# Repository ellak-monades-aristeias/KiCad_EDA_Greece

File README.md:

# Περιγραφή έργου KiCad_EDA_Greece
Αυτό το repository [https://github.com/ellak-monades-aristeias/KiCad_EDA_Greece](https://github.com/ellak-monades-aristeias/KiCad_EDA_Greece) δεν είναι ένα τυπικό λογισμικό, αλλά ένα έργο που έχει ως σκοπό την προώθηση του λογισμικού [Kicad](http://kicad.org/) στους Έλληνες χρήστες. Αυτό γίνεται υλοποιώντας τρεις ενέργειες.

* Πλήρης εξελληνισμός του περιβάλλοντος του KiCad [https://github.com/ellak-monades-aristeias/KiCad_EDA_Greece/tree/master/work/translation]
* Ανάπτυξη μίας απλής ηλεκτρονικής συσκευής ανοιχτού υλικού με το KiCad ([περισσότερες πληροφορίες](work/pcb/usb2uart/README.md)) [https://github.com/ellak-monades-aristeias/KiCad_EDA_Greece/tree/master/work/pcb/usb2uart]
* Συγγραφή ενός οδηγού εκμάθησης (tutorial) χρήσης του KiCad στα Ελληνικά χρησιμοποιώντας την ηλεκτρονική συσκευή ανοιχτού υλικού ως βάση [https://github.com/ellak-monades-aristeias/KiCad_EDA_Greece/tree/master/work/tutorial/tutorial_published]

Τα αρχεία και για τις τρεις ενέργειες αποτελούν τα αρχεία αυτού του repository. Μπορείτε να βρείτε περισσότερες πληροφορίες και για τις τρεις ενέργειες στο [KiCad_EDA_Greece Wiki](https://github.com/ellak-monades-aristeias/KiCad_EDA_Greece/wiki).

#English description of project KiCad_EDA_Greece
This repository [https://github.com/ellak-monades-aristeias/KiCad_EDA_Greece](https://github.com/ellak-monades-aristeias/KiCad_EDA_Greece) is not a typical software package, but it is a project with the intent to promote the software application named [Kicad](http://kicad.org/) to Greek users. This is implemented through three means.

* Full localization of KiCad's user interface [https://github.com/ellak-monades-aristeias/KiCad_EDA_Greece/tree/master/work/translation]
* Development of a simple, open hardware electronic device using KiCad ([more information](work/pcb/usb2uart/README.md)) [https://github.com/ellak-monades-aristeias/KiCad_EDA_Greece/tree/master/work/pcb/usb2uart]
* Write a detailed KiCad tutorial in Greek, using the above electronic device as a practical example [https://github.com/ellak-monades-aristeias/KiCad_EDA_Greece/tree/master/work/tutorial/tutorial_published]

The files for all three above actions are the files of this repository. 
You can find more information on all three actions in the [KiCad_EDA_Greece Wiki](https://github.com/ellak-monades-aristeias/KiCad_EDA_Greece/wiki).

# Λόγος ύπαρξης
Το λογισμικό KiCad είναι ένα ιδιαίτερα ισχυρό πρόγραμμα ηλεκτρονικής σχεδίασης (EDA) το οποίο υποστηρίζεται από μια μεγάλη και ενεργή ομάδα προγραμματιστών, καθώς και από το [CERN](http://home.web.cern.ch/).  
Παρότι το KiCad είναι ένα εξαιρετικά χρήσιμο και δυνατό εργαλείο σχεδίασης, δεν έχει τύχει της αναγνώρισης που του αξίζει στην Ελλάδα, καθώς οι χρήστες με περιορισμένους οικονομικούς πόρους συχνά επιλέγουν δωρεάν, αλλά κλειστές λύσεις.
Πιστεύουμε ότι ο λόγος που δεν προτιμάται το KiCad είναι η απουσία πλήρους μετάφρασης της διεπαφής του προγράμματος και η απότομη καμπύλης εκμάθησης του. 
Αυτά τα δύο στοιχεία στοχεύει να ανατρέψει αυτό το έργο.

# Εγκατάσταση και χρήση του έργου
Για οδηγίες εγκατάστασης και χρήσης του έργου δείτε το αρχείο [README_users.md](README_users.md).

# Συνεισφορά στο έργο
Για οδηγίες συνεισφοράς στο έργο δείτε το αρχείο [README_developers.md](README_developers.md).

# Χρήστες του έργου
Το εξελληνισμένο λογισμικό ηλεκτρονικής σχεδίασης KiCad μαζί με το ελληνικό tutorial μπορεί να φανεί χρήσιμο σε άτομα, οργανισμούς και επιχειρήσεις οι οποίοι θέλουν να μπορούν να σχεδιάσουν ηλεκτρονικά κυκλώματα και πλακέτες για προσωπικούς, επαγγελματικούς, και εκπαιδευτικούς λόγους. 
Σαν παράδειγμα χρηστών σε κάθε κατηγορία μπορούν να σημειωθούν οι χομπίστες ηλεκτρονικών, οι νεοφυείς επιχειρήσεις με περιορισμένους πόρους, και τα σχολεία ή ΤΕΙ.

# Οθόνη Ελληνικού περιβάλλοντος KiCad

# Ελάχιστες απαιτήσεις (προαπαιτούμενα)
Οι ελάχιστες απαιτήσεις για χρήση του εξελληνισμένου περιβάλλοντος KiCad είναι το λογισμικό KiCad. Το KiCad (έκδοση 4.0) τρέχει σε οποιονδήποτε υπολογιστή που τρέχει ένα από τα υποστηριζόμενα λειτουργικά συστήματα.
Για τον οδηγό εκμάθησης (tutorial) χρήσης του KiCad η μόνη απαίτηση είναι ένα πρόγραμμα προβολής αρχείων pdf. Για τη συσκευή ανοιχτού λογισμικού απαιτείται επίσης το λογισμικό KiCad.

# Τελικά Αποτελέσματα Έργου (Παραδοτέα)

* Παραδοτέο 1: [οδηγός εκμάθησης/tutorial χρήσης του KiCad στα Ελληνικά](https://github.com/ellak-monades-aristeias/KiCad_EDA_Greece/blob/master/work/tutorial/tutorial_published/tutorial_kicad_issue01_00.pdf)

* Παραδοτέο 2: [αρχεία κυκλώματος ανοιχτού υλικού](https://github.com/ellak-monades-aristeias/KiCad_EDA_Greece/tree/master/work/pcb/usb2uart)

* Παραδοτέο 3: [αρχεία μετάφρασης KiCad](https://github.com/ellak-monades-aristeias/KiCad_EDA_Greece/blob/master/work/translation/kicad.po)

# Άδεια χρήσης και πνευματικά δικαιώματα

Το περιεχόμενο αυτού του έργου κυκλοφορεί κάτω από άδειες EUPL v1.1 και CC-BY-SA 4.0.

**Για να δείτε το περιεχόμενο αυτών των αδειών επισκεφθείτε τα  http://creativecommons.org/licenses/by-sa/4.0/deed.el και http://ec.europa.eu/idabc/eupl.html**

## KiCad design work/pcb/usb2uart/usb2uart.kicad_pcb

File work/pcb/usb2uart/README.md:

## USB2UART: μετατροπέας USB σε 3,3V UART ανοιχτού υλικού

---

Σχηματικό κύκλωμα και σχεδίαση πλακέτας για έναν μετατροπέα USB σε 3,3V UART ανοιχτού υλικού. Υλικό για ελληνικό οδηγό εκμάθησης του KiCad.

### Το USB2UART είναι ένας βασικός μετατροπέας USB σε 3,3V UART με τα παρακάτω χαρακτηριστικά:

Η συσκευή ονομάζεται USB2UART και είναι ένας μετατροπέας USB σε 3,3V UART, βασισμένος στο ολοκληρωμένο CP2104 από την εταιρεία Silicon Labs. Συνδέεται με έναν σύνδεσμο USB type B από τη μία πλευρά και έναν απλό σύνδεσμο τεσσάρων ακροδεκτών από την άλλη. Περιλαμβάνει LED ένδειξης on/off και LED ένδειξης αποστολής/παραλαβής RX/TX.

* Βασισμένος στο ολοκληρωμένο CP2104 από την εταιρεία Silicon Labs.
* Υποστηρίζεται από τα περισσότερα σύγχρονα λειτουργικά συστήματα ως εικονική σειριακή θύρα.
* Διαθέτει έναν σύνδεσμο USB τύπου B από τη μία πλευρά και έναν απλό σύνδεσμο τεσσάρων ακροδεκτών (pin header) από την άλλη
* Περιλαμβάνει LED ένδειξης on/off και LED ένδειξης αποστολής/παραλαβής RX/TX.
* Έχει υλοποιηθεί ως πλακέτα τυπωμένου κυκλώματος (PCB) δύο επιπέδων χρησιμοποιώντας το [KiCAD EDA software suite](http://www.kicad.org).
* Ανοιχτό υλικό.

---

### Διάγραμμα μπλοκ

---

### Λίστα αρχείων

* **README.md:** αυτό το αρχείο
* **usb2uart.pro:** αρχείο έργου KiCAD
* **usb2uart.sch:** σχηματικό κύκλωμα
* **usb2uart.pdf:** σχηματικό κύκλωμα τυπωμένο σε PDF
* **usb2uart.lib:** βιβλιοθήκη προσαρμοσμένων εξαρτημάτων
* **usb2uart-cache.lib:** προσωρινή αποθήκευση βιβλιοθήκης όλων των εξαρτημάτων
* **usb2uart.dcm:** βιβλιοθήκη τεκμηρίωσης εξαρτημάτων
* **usb2uart.net:** λίστα δικτύων
* **usb2uart.kicad_pcb:** σχεδίαση πλακέτας
* **usb2uart.csv:** λίστα υλικών (BOM)
* **usb2uart.pretty/:** βιβλιοθήκη προσαρμοσμένων αποτυπωμάτων
* **contrib/:** 3Δ μοντέλα από τρίτους. Πολλές ευχαριστίες στον [Walter](http://smisioto.no-ip.org/elettronica/kicad/kicad-en.htm) για τη διανομή της δουλειάς του σε [CC-BY-SA 3.0](http://creativecommons.org/licenses/by-sa/3.0/)
* **datasheets/:** εγχειρίδια/φύλλα δεδομένων (datasheets) για όλα τα εξαρτήματα
* **images/:** διάφορες εικόνες
* **mfg/usb2uart.drl:** αρχείο διάτρησης excellon CNC
* **mfg/usb2uart-all.pos:** αρχείο τοποθέτησης εξαρτημάτων SMD για μηχανές ανύψωσης και τοποθέτησης
* **mfg/gerber/:** αρχεία gerber

---

### Άδεια χρήσης και πνευματικά δικαιώματα

**© 2014-2015 Logikon Labs.**

**Όλα τα αρχεία σχεδίασης και παραγωγής είναι διαθέσιμα με άδειες [Creative Commons Attribution-ShareAlike 4.0 International License](http://creativecommons.org/licenses/by-sa/4.0/).**

**Για να δείτε το περιεχόμενο αυτής της άδειας χρήσης επισκεφθείτε το http://creativecommons.org/licenses/by-sa/4.0/deed.el.**

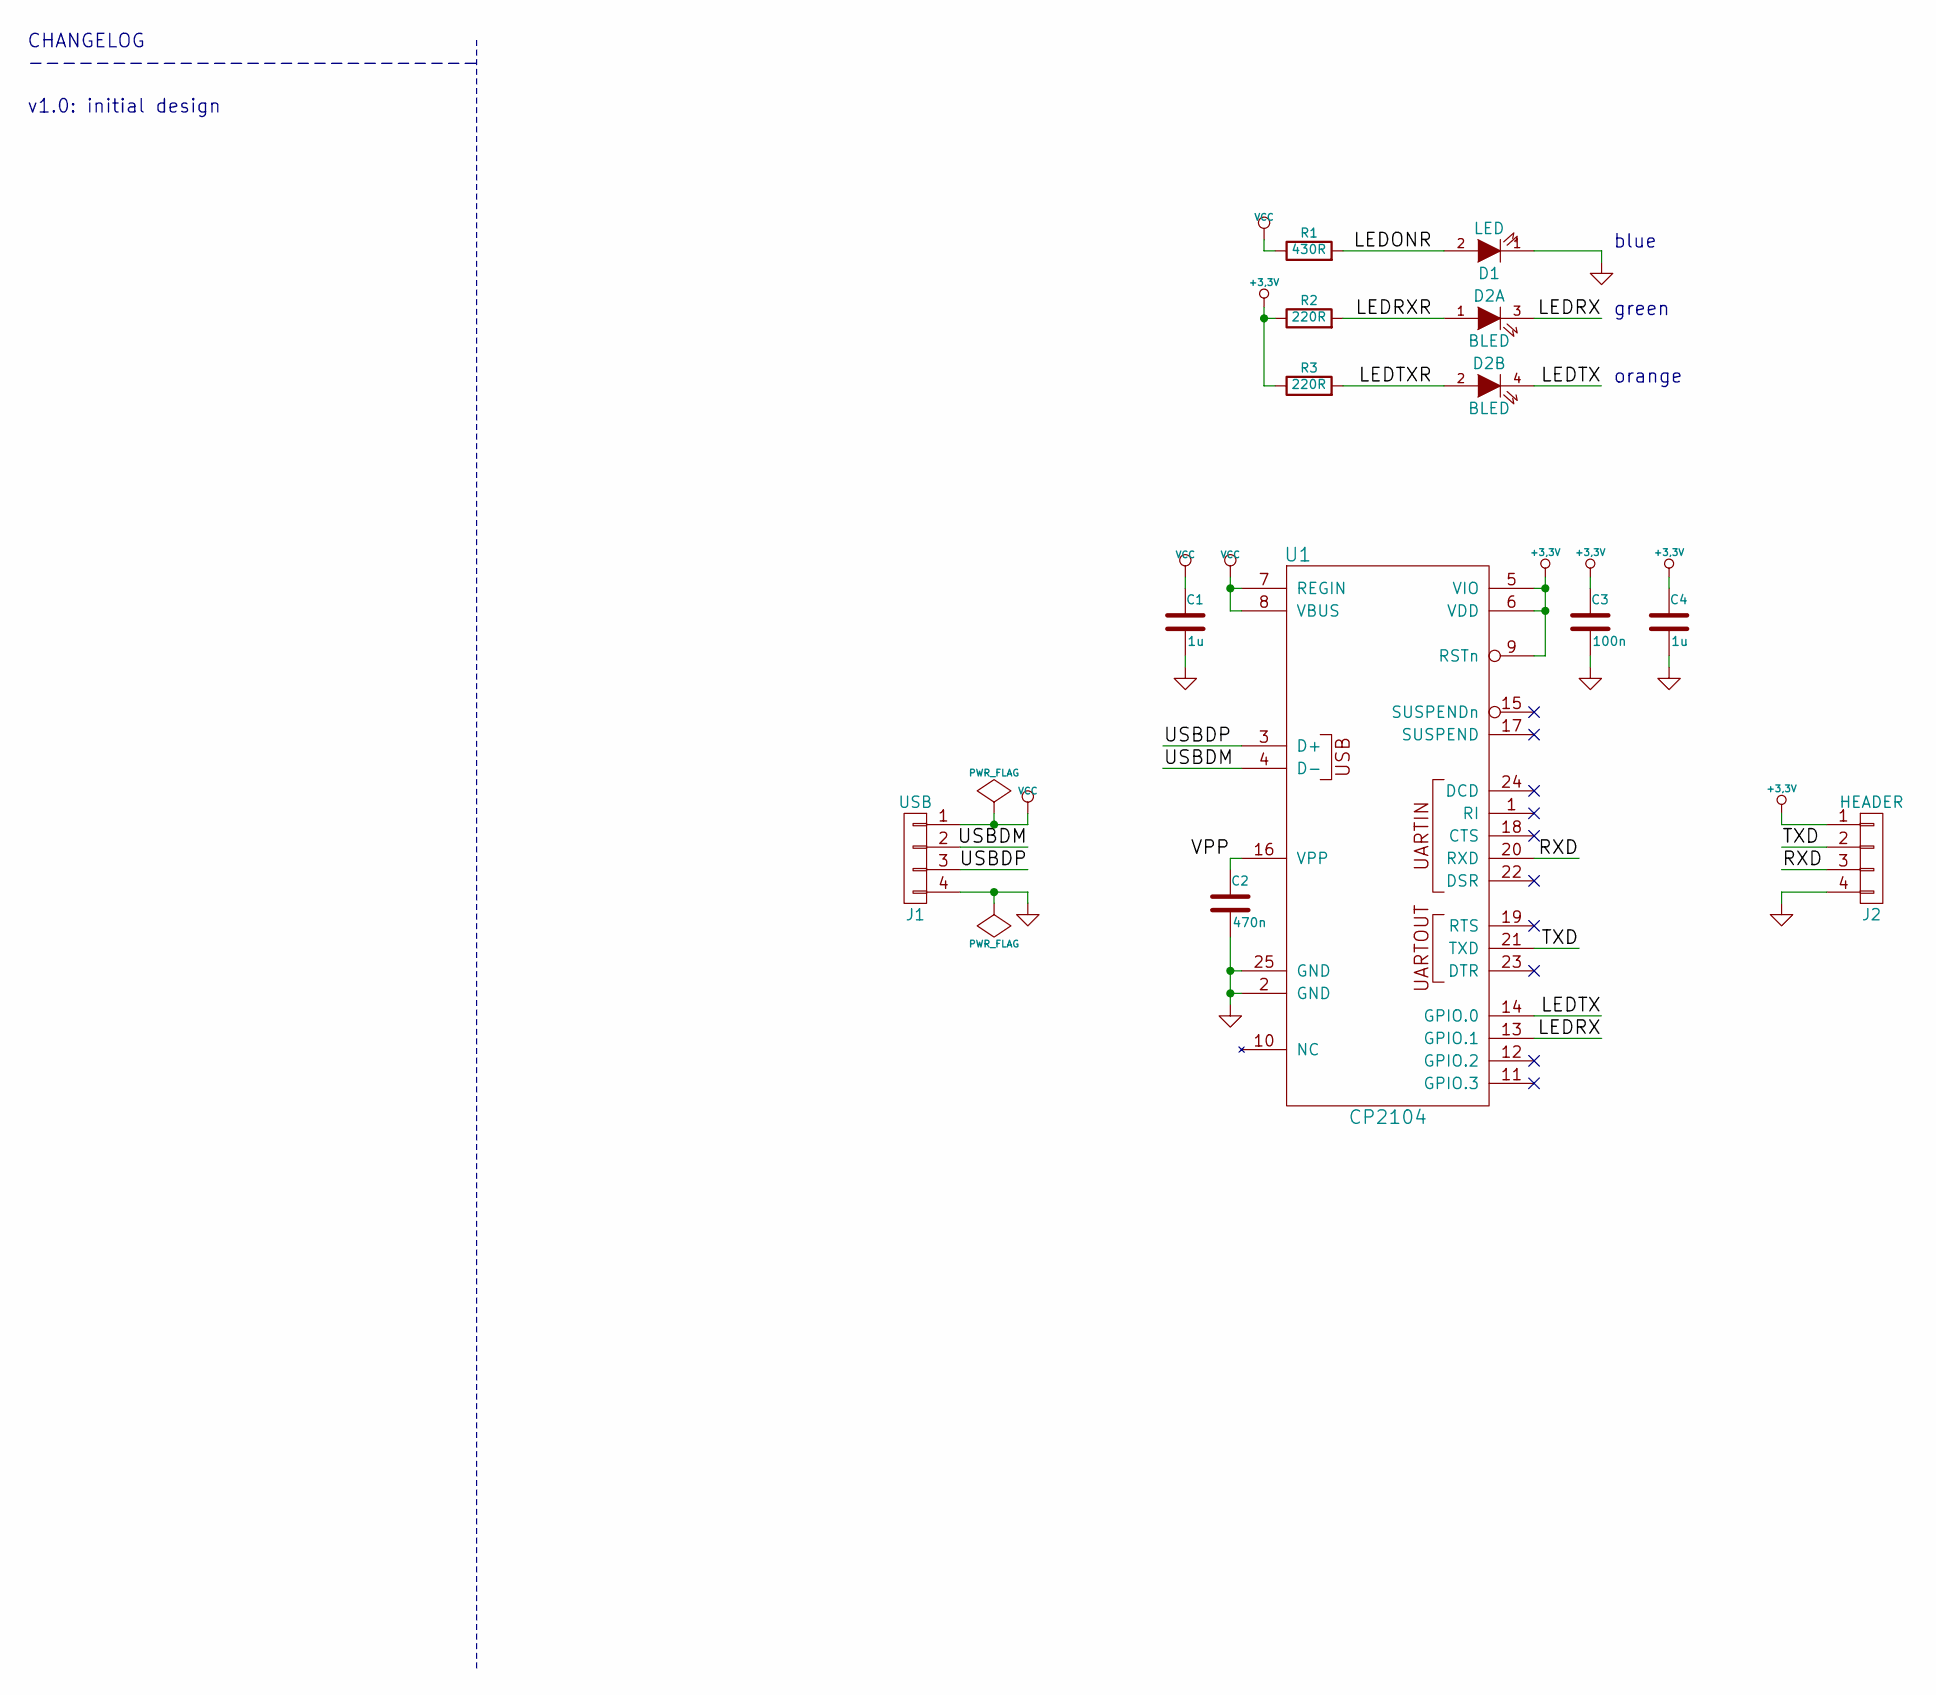
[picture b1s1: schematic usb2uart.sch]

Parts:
C1, C4: 1u; C_0402
C2: 470n; C_0402
C3: 100n; C_0402
D1: LED; LED-0603
D2: BLED; bled_0603
J1: USB; USB_B
J2: HEADER; Pin_Header_Angled_1x04
R1: 430R; R_0402
R2, R3: 220R; R_0402
U1: CP2104; qfn24

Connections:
+3.3V: C3.1, C4.1, J2.1, R2.1, R3.1, U1.5 (VIO), U1.6 (VDD), U1.9 (RSTn)
/LEDONR: D1.2 (A), R1.2
/LEDRX: D2.3 (K), U1.13 (GPIO.1)
/LEDRXR: D2.1 (A), R2.2
/LEDTX: D2.4 (K), U1.14 (GPIO.0)
/LEDTXR: D2.2 (A), R3.2
/RXD: J2.3, U1.20 (RXD)
/TXD: J2.2, U1.21 (TXD)
/USBDM: J1.2, U1.4 (D-)
/USBDP: J1.3, U1.3 (D+)
/VPP: C2.1, U1.16 (VPP)
GND: C1.2, C2.2, C3.2, C4.2, D1.1 (K), J1.4, J2.4, U1.2 (GND), U1.25 (GND)
VCC: C1.1, J1.1, R1.1, U1.7 (REGIN), U1.8 (VBUS)

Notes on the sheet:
CHANGELOG --------------------------- v1.0: initial design
blue
green
orange

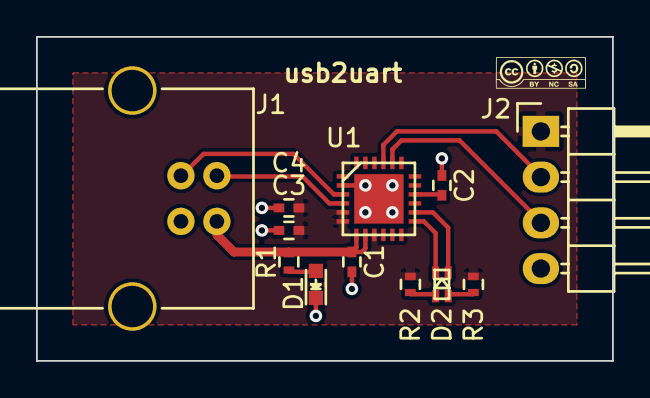
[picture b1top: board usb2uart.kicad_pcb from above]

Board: 2 copper layers, 32.0 x 18.0 mm, 12 parts (0 on the bottom side), 13 nets.

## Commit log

2015-08-26 [doc] Συγγραφή readme.md
2015-08-27 [transl] Προσθήκη ελληνικού .po από bazaar commit revno: 866
2015-08-27 [transl] Ανανεώθηκαν τα αρχεία .po με βάση τον κώδικα με github hash 2e4136720dbe98facf8888f714fa4418228af49b
2015-08-27 [transl] Ολοκλήρωση μετάφρασης αρχικής οθόνης (εκτός προγραμμάτων)
2015-08-28 [transl] Ολοκλήρωση μετάφρασης αρχικής οθόνης και υποεπιλογών (εκτός προγραμμάτων)
2015-09-01 [transl] Μετάφραση κύριων εννοιών (via, schematic, κοκ)
2015-09-01 [transl] Μετάφραση βασικών εννοιών και μερικώς EEschema
2015-09-02 [transl] Μετάφραση μεγαλύτερου μέρους μενού EEschema
2015-09-03 [transl] Ολοκλήρωση μενού και κουμπιών αρχικής σελίδας Eeschema
2015-09-03 [transl] Ολοκλήρωση μενού έως και Τοποθέτηση (και παιδιών) αρχικής σελίδας Eeschema
2015-09-04 [transl] Ολοκλήρωση μενού έως και Προτιμήσεις (και παιδιών) αρχικής σελίδας Eeschema
2015-09-04 [transl] Ολοκλήρωση αρχικής σελίδας component editor
2015-09-04 [transl] Μετάφραση strings σχετικά με αρχεία
2015-09-10 [transl] Μετάφραση μενού (πλήρες βάθος) σε component editor
2015-09-10 [transl] Ολοκλήρωση μετάφρασης component editor
2015-09-10 [transl] Μετάφραση Eeschema
2015-09-11 [pcb] Πρώτη έκδοση (ημιτελής) του κυκλώματος
2015-09-11 [transl] Ολοκλήρωση μετάφρασης Eeschema, component editor (99%)
2015-09-14 [transl] Μετάφραση κειμένων CvPCB
2015-09-14 [transl] Ολοκλήρωση μετάφρασης Cvpcb και σχετικών εργαλείων (99%)
2015-09-14 [transl] Αλλαγή μετάφραση annotate και reference
2015-09-14 [transl] Μετάφραση κειμένων PCBnew
2015-09-15 [transl] Μετάφραση αρχικής οθόνης footprint editor
2015-09-15 [transl] Ολοκλήρωση μετάφρασης footprint editor (99%)
2015-09-16 [transl] Μετάφραση γενικών κειμένων
2015-09-17 [transl] Ολοκλήρωση μετάφρασης αρχικής σελίδας PCBnew
2015-09-17 [transl] Ολοκλήρωση όλων των fuzzy
2015-09-18 [transl] Ολοκλήρωση μετάφρασης PCBnew (έως και δεύτερο επίπεδο)
2015-09-18 [transl] Μετάφραση διάφορων κειμένων
2015-09-22 [transl] Ολοκλήρωση μετάφρασης 100% (προ ελέγχων)
2015-09-23 [transl] Διορθώσεις μεταφράσεων, ορισμός συντομεύσεων &
2015-09-23 [transl] Ορισμός συντομεύσεων &
2015-09-23 [transl] Αλλαγή γλώσσας σε el
2015-09-23 [transl] Διαγραφή περιττών σχολίων
2015-09-24 [transl] Ορισμός σωστών συντομεύσεων (&) σε όλα τα μενού
2015-09-25 [transl] Διορθώσεις κειμένων
2015-09-25 [pcb] πρώτη ολοκληρωμένη έκδοση κυκλώματος, μαζί με αρχεία παραγωγής
2015-09-25 [pcb] fixed typo in README.md
2015-09-25 ενημέρωση κεντρικού αρχείου README
2015-10-02 [tut] Σχεδιασμός κεφαλαίων και περιεχομένου του tutorial
2015-10-07 [transl] Ανανέωση Ελληνικού .po με πηγαίο κώδικα από revision 6215
2015-10-07 [transl] 100% πλήρης και ελεγμένη μετάφραση για revision 6215 του πηγαίου κώδικα
2015-10-07 ανανέωση .gitignore
2015-10-07 [tut] Δημιουργία αρχείου tutorial, πρώτα κείμενα
2015-10-07 [tut] Ολοκλήρωση κεφαλαίου δημιουργίας σχηματικού
2015-10-08 [tut] Προσθήκη αρχείου pdf για το tutorial
2015-10-08 Προσθήκη οδηγιών εγκατάστασης
2015-10-08 [tut] Ολοκλήρωση κεφαλαίου προσθήκης εξαρτημάτων
2015-10-08 [tut] Κείμενα κεφαλαίου δημιουργίας εξαρτημάτων
2015-10-09 [tut] Διόρθωση κεφαλαίου προσθήκης εξαρτημάτων
2015-10-12 [tut] Ολοκλήρωση κεφαλαίου προσθήκης/επεξεργασίας εξαρτημάτων πολλών μερών
2015-10-13 Προσθήκη αρχείων για βήματα tutorial
2015-10-13 [tut] Ολοκλήρωση tutorial σχηματικού
2015-10-14 [tut] Ολοκλήρωση κεφαλαίου οριστικής τοποθέτηση αποτυπωμάτων
2015-10-14 Ενημέρωση README.md
2015-10-14 Δημιουργία αρχείου 'ταυτότητα έργου'
2015-10-14 [tut] Ολοκλήρωση tutorial, πρώτη έκδοση
2015-10-14 Προσθήκη αρχείου .gitignore
2015-10-14 [transl] Μικρές διορθώσεις μετάφρασης
2015-10-14 [tut] Προσθήκη εικόνων στο tutorial
2015-10-15 [tut] Αναθεώρηση κεφαλαίου για αρχεία που χρησιμοποιεί το Kicad
2015-10-15 [tut] Ολοκλήρωση tutorial (1.0)
2015-10-20 Ενημέρωση αρχείων .md
2015-10-20 Προσθήκη ταυτότητας έργου σε pdf
2015-10-23 Προσθήκη αρχείων .md για χρήστες και developers
2015-10-23 Ενημέρωση ταυτότητας έργου
2015-10-23 Ενημέρωση οδηγιών για developers
2015-10-30 [transl] Ανανέωση μετάφρασης για αρχεία κώδικα bzr revision 6286
2015-11-04 [transl] Ανανέωση μετάφρασης για αρχεία κώδικα bzr revision 6298
2015-11-04 [transl] Διορώσεις μετάφρασης
2015-11-05 Ανανέωση οδηγιών για developers
2015-11-05 [transl] Διορθώσεις μετάφρασης
2015-11-05 [tut] Ανανέωση tutorial, διόρθωση λαθών, νέα έκδοση (1.1)
2015-11-06 [tut] Ανανέωση tutorial, διόρθωση λαθών, νέα έκδοση (1.2)
2015-11-06 [tut] Ανανέωση tutorial, προσθήκη νέων αρχείων για ενδιάμεσα στάδια, νέα έκδοση (1.5)
2015-11-16 Αγγλική περιγραφή έργου στο README.md
2015-11-20 [transl] Ανανέωση μετάφρασης (rev 6326)
2015-11-20 Ανανέωση README.md με αναφορές στο Wiki
2015-11-23 Διόρθωση τυπογραφικού λάθους στο README.md
2015-11-24 Προσθήκη links προς αρχεία στο README.md
2016-01-03 [transl] Ενημερωση μεταφρασης απο bzr 6413
2016-01-03 [transl] Ολοκλήρωση μεταφρασης bzr 6413
2016-03-25 [transl] Ενημερωση μεταφρασης απο bzr 6648
2016-03-25 [transl] Ολοκλήρωση μετάφρασης απο bzr 6648
2016-04-09 Ενημέρωση αμετάφραστων κειμένων από bzr commit 6677
2016-06-12 [transl] Ολοκλήρωση μετάφρασης απο bzr 6677
2016-06-12 [transl] Ενημέρωση αμετάφραστων αρχείων από bzr 6923
2016-06-12 [transl] Ολοκλήρωση μετάφρασης απο bzr 6923
2016-06-18 [transl] Ενημέρωση αμετάφραστων αρχείων από bzr 6941
2016-06-18 [transl] Ολοκλήρωση μετάφρασης από KiCad source code bzr commit 6941
2016-06-25 [transl] Ενημέρωση αμετάφραστων αρχείων από KiCad source code bzr commit 6946
2016-07-02 [transl] Ενημέρωση αμετάφραστων αρχείων από KiCad source code bzr commit 6960
2016-09-10 [transl] Ενημέρωση αμετάφραστων αρχείων από KiCad source code git commit 7318238daa
2016-12-08 [transl] Ολοκλήρωση μετάφρασης από KiCad source code commit 7318238daa
2016-12-08 [transl] Ενημέρωση αμετάφραστων αρχείων από KiCad source code git commit 3d89fb640a
2016-12-25 [transl] Ολοκλήρωση μετάφρασης από KiCad source code commit 3d89fb640a
2017-01-28 [transl] Ενημέρωση αμετάφραστων αρχείων από KiCad source code commit d0c46a81d9
2017-01-28 [transl] Ολοκλήρωση μετάφρασης από KiCad source code commit d0c46a81d9
2017-02-25 [transl] Ενημέρωση αμετάφραστων αρχείων από KiCad source code commit e6de99cc86
2017-02-25 [transl] Ολοκλήρωση μετάφρασης από KiCad source code commit e6de99cc86
2017-09-27 [transl] Ενημέρωση αμετάφραστων αρχείων από KiCad source code commit 9ca3f632a2
2017-11-18 [transl] Ολοκλήρωση μετάφρασης από KiCad source code commit 9ca3f632a2
2017-11-18 [transl] Ενημέρωση αμετάφραστων αρχείων από KiCad source code commit d5d08d3677
2018-04-06 [transl] Ενημέρωση αμετάφραστων αρχείων από KiCad source code commit 94dbcc7199
2018-09-23 [transl] Ενημέρωση αμετάφραστων αρχείων από KiCad source code commit ae13e441af
2018-10-07 [transl] Work In Progress μετάφραση από KiCad source code commit ae13e441af
2018-10-07 [transl] Ενημέρωση αμετάφραστων αρχείων από KiCad source code commit 1ee579c821
2018-11-27 [transl] Ενημέρωση αμετάφραστων αρχείων από KiCad source code commit db07b43674
2019-01-12 [transl] Work In Progress μετάφραση από KiCad source code commit db07b43674
2019-01-12 [transl] Ενημέρωση αμετάφραστων αρχείων από KiCad source code commit a0a4e5e18d
2019-04-28 [transl] Ενημέρωση αμετάφραστων αρχείων από KiCad source code commit e808c7f956
2019-05-04 [transl] Ενημέρωση αμετάφραστων αρχείων από KiCad source code commit f87754848e
2019-05-05 [transl] Ενημέρωση αμετάφραστων από KiCad 5.1.0, work in progress μετάφραση απομένει 17%
2019-05-05 [transl] Ενημέρωση αμετάφραστων αρχείων από KiCad source code commit f87754848e, μέσω kicad-i18n/update-po-files.sh
2019-07-03 work in progress μετάφραση απομένει 16%
2019-07-03 [transl] Ενημέρωση αμετάφραστων αρχείων από KiCad source code commit c715a22e1c
2019-09-09 [transl] work in progress μετάφραση απομένει 22%
2019-09-09 [transl] Ενημέρωση αμετάφραστων αρχείων από KiCad source code commit 8dd8740fa3
2019-09-09 [transl] work in progress μετάφραση απομένει 25%
2019-09-12 [transl] work in progress μετάφραση απομένει 18%
2019-09-16 [transl] work in progress μετάφραση απομένει 16%
2019-09-17 [transl] work in progress μετάφραση απομένει 15%
2019-09-18 [transl] work in progress μετάφραση απομένει 14%
2019-09-18 [transl] Ενημέρωση αμετάφραστων αρχείων από KiCad source code commit a1fe8cfa5a
2019-09-26 [transl] work in progress μετάφραση απομένει 9%
2019-09-26 [transl] Ενημέρωση αμετάφραστων αρχείων από KiCad source code commit 281d77f6b3
2019-09-27 [transl] work in progress μετάφραση απομένει 6%
2019-10-01 [transl] μετάφραση 100%, μερικά θέλουν ακόμα δουλειά
2019-10-04 [transl] Ενημέρωση αμετάφραστων αρχείων από KiCad source code
2019-10-05 [transl] μετάφραση 100%, 22 θέλουν βελτίωση
2019-10-29 [transl] μετάφραση 100%, 14 θέλουν βελτίωση
2021-11-11 [transl] work in progress μετάφραση απομένει 6%, πρώτη φορά για https://hosted.weblate.org/projects/kicad/master-source/el/
2021-11-11 [transl] work in progress μετάφραση απομένει 6%
    Πρωτη φορά μέσω https://hosted.weblate.org/projects/kicad/master-source/el/
